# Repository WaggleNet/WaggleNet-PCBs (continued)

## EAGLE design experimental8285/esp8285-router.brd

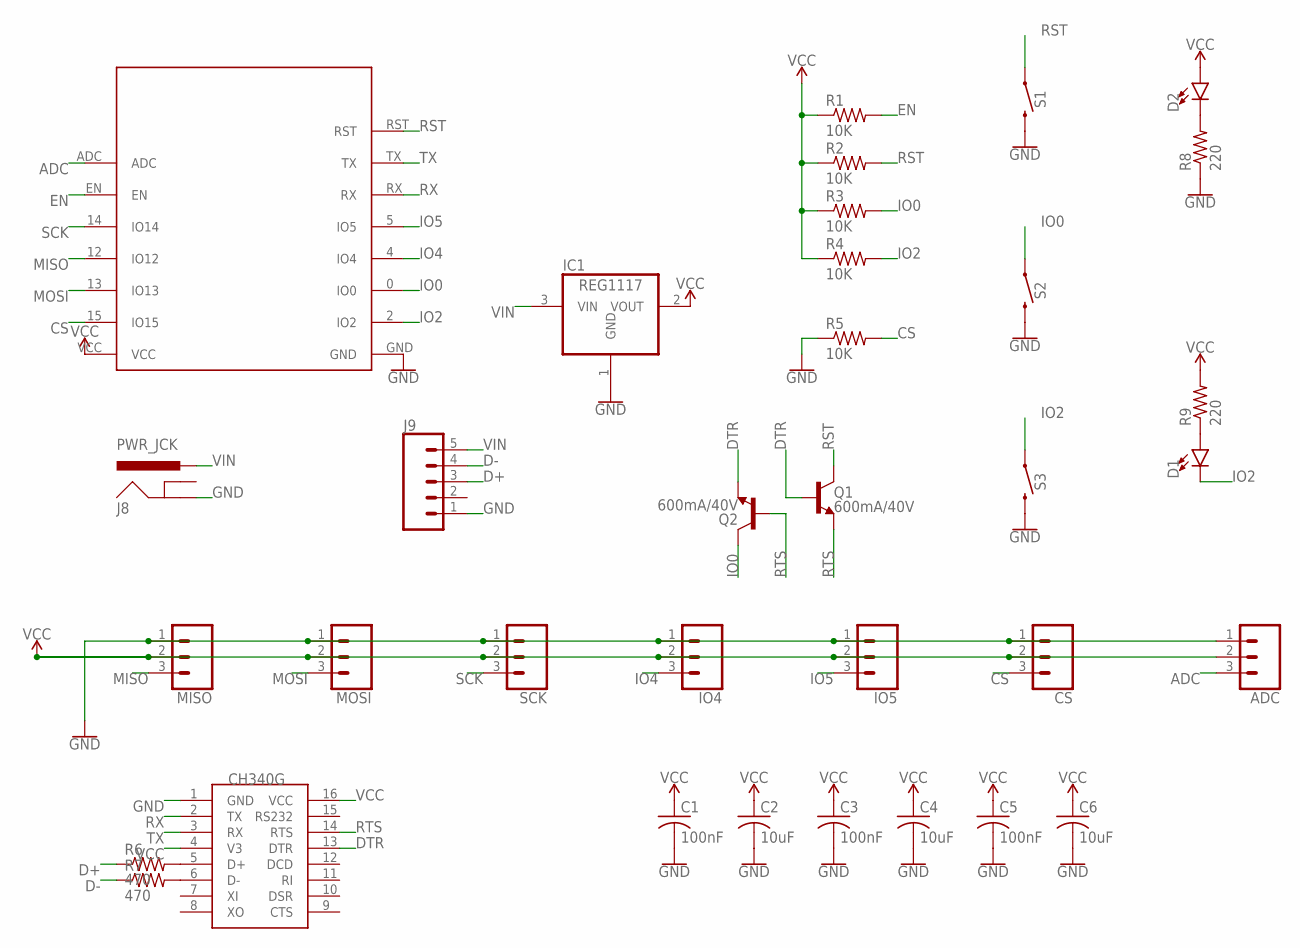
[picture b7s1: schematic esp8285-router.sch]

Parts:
ADC: CONN_03; 1X03
C1, C3, C5: 100nF; C1206
C2, C4, C6: 10uF; C1206
CH340C: CH340C; SOIC16
CS: CONN_03; 1X03
D1, D2: LED1206; LED-1206
IC1: REG1117; SOT223
IO4, IO5: CONN_03; 1X03
J8: PWR_JCK; POWER_JACK_SLOT
J9: CONN_05; 1X05
MISO: CONN_03; 1X03
MOSI: CONN_03; 1X03
Q1, Q2: 600mA/40V; SOT23-3
R1, R2, R3, R4, R5: 10K; R1206
R6, R7: 470; R1206
R8, R9: 220; R1206
S1, S2, S3: MOMENTARY-SWITCH-SPST-PTH-6.0MM; TACTILE_SWITCH_PTH_6.0MM
SCK: CONN_03; 1X03
U$1: ESP-M2

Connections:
ADC: ADC.3, U$1.ADC
CS: CS.3, R5.2, U$1.15 (IO15)
D+: J9.3, R6.1
D-: J9.4, R7.1
DTR: CH340C.13 (DTR), Q1.1 (B), Q2.2 (E)
EN: R1.2, U$1.EN
GND: ADC.1, C1.2, C2.2, C3.2, C4.2, C5.2, C6.2, CH340C.1 (GND), CS.1, IC1.1 (GND), IO4.1, IO5.1, J8.GND@2 (GND), J9.1, MISO.1, MOSI.1, R5.1, R8.1, S1.3 (2), S2.3 (2), S3.3 (2), SCK.1, U$1.GND
IO0: Q2.3 (C), R3.2, S2.1, U$1.0 (IO0)
IO2: D1.C, R4.2, S3.1, U$1.2 (IO2)
IO4: IO4.3, U$1.4 (IO4)
IO5: IO5.3, U$1.5 (IO5)
MISO: MISO.3, U$1.12 (IO12)
MOSI: MOSI.3, U$1.13 (IO13)
unnamed: CH340C.5 (D+), R6.2
unnamed: CH340C.6 (D-), R7.2
unnamed: D1.A, R9.1
unnamed: D2.C, R8.2
RST: Q1.3 (C), R2.2, S1.1, U$1.RST
RTS: CH340C.14 (RTS), Q1.2 (E), Q2.1 (B)
RX: CH340C.2 (TX), U$1.RX
SCK: SCK.3, U$1.14 (IO14)
TX: CH340C.3 (RX), U$1.TX
VCC: ADC.2, C1.1, C2.1, C3.1, C4.1, C5.1, C6.1, CH340C.4 (V3), CH340C.16 (VCC), CS.2, D2.A, IC1.2 (VOUT), IO4.2, IO5.2, MISO.2, MOSI.2, R1.1, R2.1, R3.1, R4.1, R9.2, SCK.2, U$1.VCC
VIN: IC1.3 (VIN), J8.PWR, J9.5

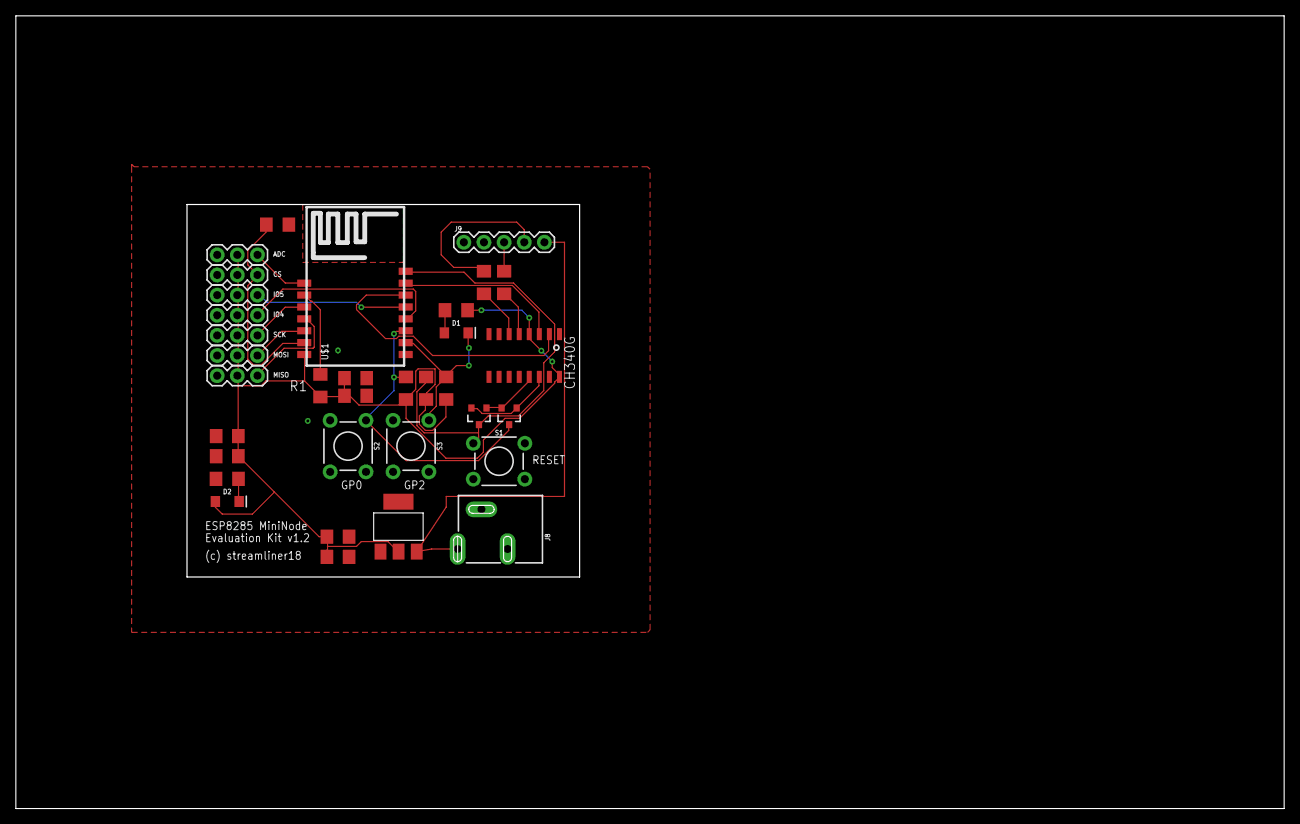
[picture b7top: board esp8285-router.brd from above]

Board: 2 copper layers, 159.8 x 99.8 mm, 34 parts (0 on the bottom side), 24 nets.

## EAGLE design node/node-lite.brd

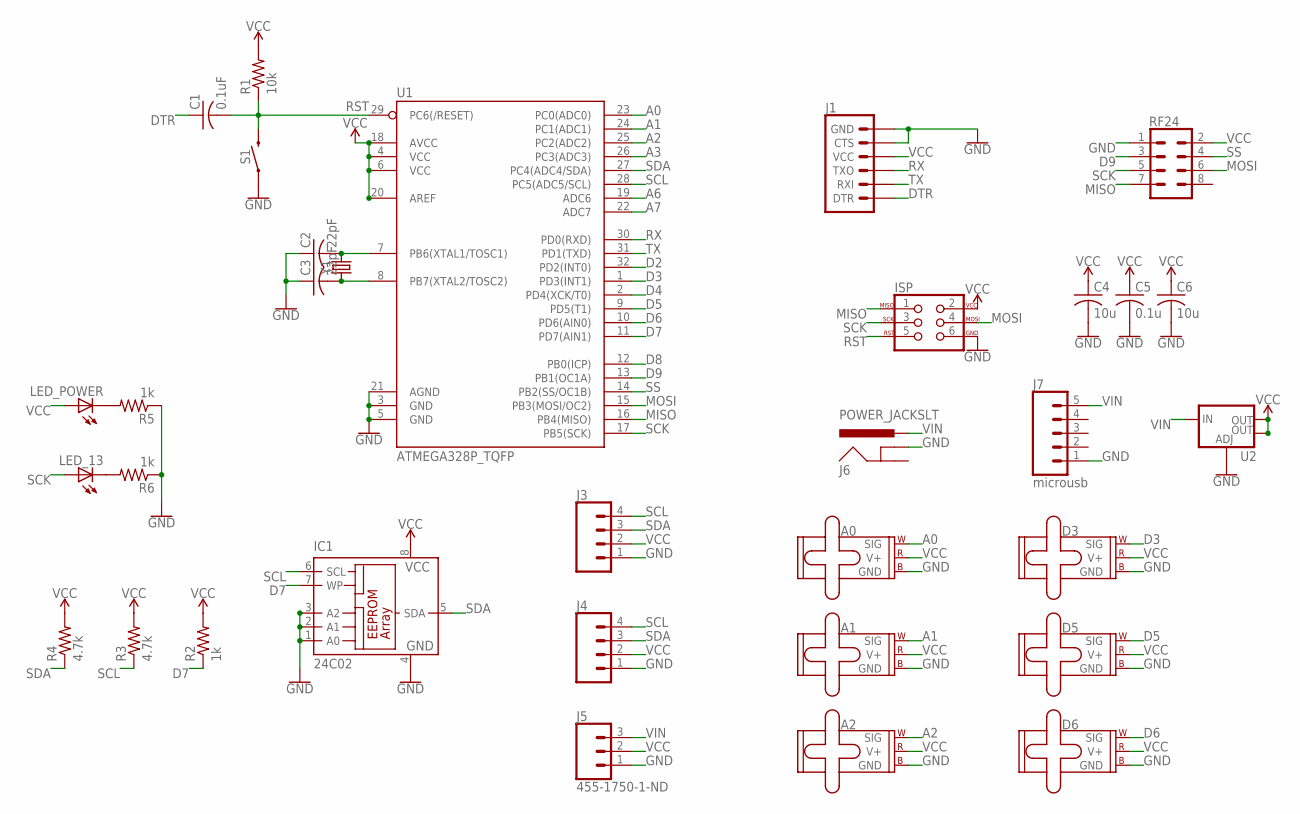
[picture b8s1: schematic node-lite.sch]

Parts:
A0, A1, A2: SERVO; 1X03
C1: 0.1uF; C1206
C2, C3: 22pF; C1206
C4, C6: 10u; C1206
C5: 0.1u; C1206
D3, D5, D6: SERVO; 1X03
IC1: 24C02; SO-08
ISP: AVR_SPI_PROG_3X2NS; 2X3-NS
J1: 6_PIN_SERIAL_TARGET; 1X06
J3, J4: CONN_04; 1X04
J5: 455-1750-1-ND; 1X03
J6: POWER_JACKSLT; POWER_JACK_SLOT
J7: microusb; 1X05
LED_13: LEDCHIPLED_1206; CHIPLED_1206
LED_POWER: LEDCHIPLED_1206; CHIPLED_1206
R1: 10k; R1206
R2, R5, R6: 1k; R1206
R3, R4: 4.7k; R1206
RF24: CONN_04X2; 2X4
S1: MOMENTARY-SWITCH-SPST-PTH-6.0MM; TACTILE_SWITCH_PTH_6.0MM
U1: ATMEGA328P_TQFP; TQFP32-08
U2: V_REG_LM1117SOT223; SOT223
Y1: CRYSTALPTH-HC49US; HC49US

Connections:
A0: A0.1 (SIG), U1.23 (PC0(ADC0))
A1: A1.1 (SIG), U1.24 (PC1(ADC1))
A2: A2.1 (SIG), U1.25 (PC2(ADC2))
A3: U1.26 (PC3(ADC3))
A6: U1.19 (ADC6)
A7: U1.22 (ADC7)
D2: U1.32 (PD2(INT0))
D3: D3.1 (SIG), U1.1 (PD3(INT1))
D4: U1.2 (PD4(XCK/T0))
D5: D5.1 (SIG), U1.9 (PD5(T1))
D6: D6.1 (SIG), U1.10 (PD6(AIN0))
D7: IC1.7 (WP), R2.1, U1.11 (PD7(AIN1))
D8: U1.12 (PB0(ICP))
D9: RF24.3, U1.13 (PB1(OC1A))
DTR: C1.1, J1.1 (DTR)
GND: A0.3 (GND), A1.3 (GND), A2.3 (GND), C2.1, C3.1, C4.2, C5.2, C6.2, D3.3 (GND), D5.3 (GND), D6.3 (GND), IC1.1 (A0), IC1.2 (A1), IC1.3 (A2), IC1.4 (GND), ISP.6, J1.5 (CTS), J1.6 (GND), J3.1, J4.1, J5.1, J6.GND@1 (GNDBREAK), J7.1, R5.1, R6.1, RF24.1, S1.1, U1.3 (GND), U1.5 (GND), U1.21 (AGND), U2.1 (ADJ)
MISO: ISP.1, RF24.7, U1.16 (PB4(MISO))
MOSI: ISP.4, RF24.6, U1.15 (PB3(MOSI/OC2))
unnamed: C2.2, U1.7 (PB6(XTAL1/TOSC1)), Y1.2
unnamed: C3.2, U1.8 (PB7(XTAL2/TOSC2)), Y1.1
unnamed: LED_POWER.C, R5.2
unnamed: LED_13.C, R6.2
RST: C1.2, ISP.5, R1.1, S1.3 (2), U1.29 (PC6(/RESET))
RX: J1.3 (TXO), U1.30 (PD0(RXD))
SCK: ISP.3, LED_13.A, RF24.5, U1.17 (PB5(SCK))
SCL: IC1.6 (SCL), J3.4, J4.4, R3.1, U1.28 (PC5(ADC5/SCL))
SDA: IC1.5 (SDA), J3.3, J4.3, R4.1, U1.27 (PC4(ADC4/SDA))
SS: RF24.4, U1.14 (PB2(SS/OC1B))
TX: J1.2 (RXI), U1.31 (PD1(TXD))
VCC: A0.2 (V+), A1.2 (V+), A2.2 (V+), C4.1, C5.1, C6.1, D3.2 (V+), D5.2 (V+), D6.2 (V+), IC1.8 (VCC), ISP.2, J1.4 (VCC), J3.2, J4.2, J5.2, LED_POWER.A, R1.2, R2.2, R3.2, R4.2, RF24.2, U1.4 (VCC), U1.6 (VCC), U1.18 (AVCC), U1.20 (AREF), U2.2 (OUT), U2.4 (OUT)
VIN: J5.3, J6.PWR, J7.5, U2.3 (IN)

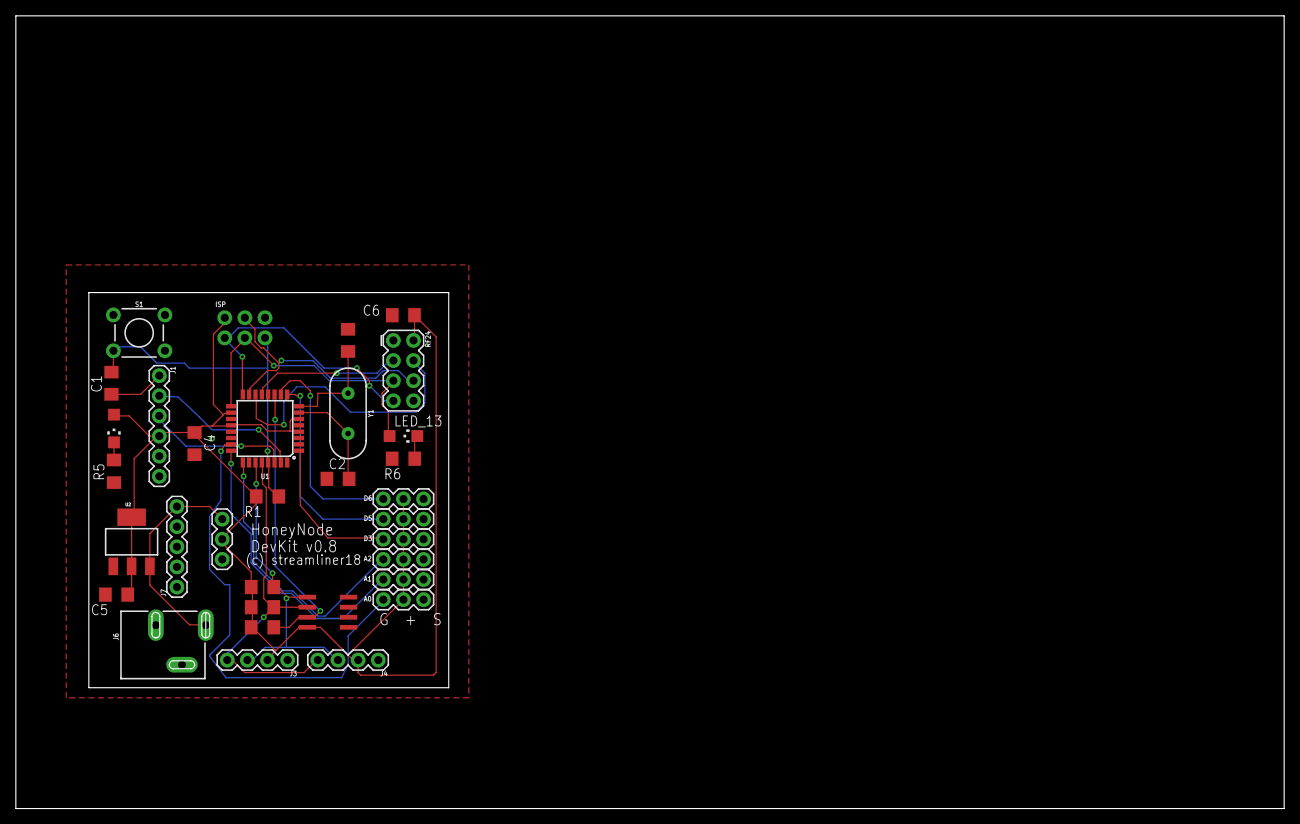
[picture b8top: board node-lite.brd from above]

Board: 2 copper layers, 160.0 x 100.0 mm, 33 parts (0 on the bottom side), 25 nets.

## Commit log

2018-02-06 Added CAM Profile
2018-04-09 Double-sided Node Trial Run v0.3b
2018-04-19 Node: v4
2018-04-19 Sensor Development board
2018-04-20 Node: Tweaked TP4056 activation point
2018-04-20 Router PCB
2018-05-01 Sensor Template: Draft for test run 1
2018-05-02 Revert "Router PCB"
    This reverts commit 5cfdc418179729a7dd419c7a517ca3d373416e11.
2018-05-03 Two sensor examples
2018-05-04 [node] Larger hole sizes (M2)
2018-05-04 [sensor] Debug connector now complies to node arrangement
2018-05-31 Node: Adding interrupt pin
2018-07-03 Eagle 8.3 Upgrade Info
2018-07-03 Programming Jig
2018-07-03 Node Double v0.6
    - Rounded PCB Corner
    - Switched to Tented Vias
    - Large M3 Mounting Hole
    - LEDs slightly distant from the RF module pins
    - Cutout copper from beneath the RF antenna
2018-07-06 Scratch progress
2018-07-10 Router PCB 1.3
2018-07-10 Routing & VCC Optimization
2018-07-11 Routing massively cleaned up
2018-07-11 Removal of Sparkfun submodule
2018-07-11 Mini Variant of Router
2018-11-11 Optional pullup on I2C + Default I2C0
2019-04-07 Node 0.8: Pour cutout for radio antenna
2019-04-07 New router 1.3
2019-04-07 Sensor dev board 1.4
2020-02-19 weigh scale pcb 1.0
2020-02-19 moved weigh scale stuff into folder
2020-02-19 Weighing scale PCB v1.0 routed and linked to Fusion
2020-10-20 Post-ramp circuit fixes
